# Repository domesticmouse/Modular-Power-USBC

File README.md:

# Modular-Power-USBC

## Project Overview
This project provides a compact, high-efficiency power solution for modular electronics (such as Eurorack synthesizers or analog prototyping boards). It converts standard **5V USB-C power** into clean, dual **±12V rails**.

### Key Features
- **USB-C Input:** Uses a power-only 6-pin receptacle for durability and simplicity.
- **Dual Rail Output:** Provides ±12V at up to 83mA per rail (2W total).
- **Comprehensive Protection:** Features overcurrent, reverse polarity, and back-drive protection.
- **Controlled Startup:** Integrated load switch with a physical toggle for safe power-up.
- **Indicator LEDs:** Visual confirmation for both positive and negative rails.

### Main Technologies
- **EDA Tool:** KiCad (Project files version 20260306, KiCad 10.0 or newer).
- **Major Components:**
  - **DC-DC Converter:** `A0512S-2WR2` (Isolated 2W module).
  - **Ideal Diode:** `LM66100` (Reverse polarity & back-drive protection).
  - **Load Switch:** `TPS22918` (Gated power control).
  - **Filtering:** Ferrite bead and 0805 SMD decoupling capacitors.
  - **Protection:** Resettable Polyfuse (`F1`).

## Circuit Architecture
The power path is designed for reliability and safety:

1.  **Input & Filtering:** 5V enters via `J1`. It is immediately protected by a Polyfuse and filtered by a Ferrite Bead to reduce high-frequency noise.
2.  **Polarity Protection:** An `LM66100` ideal diode provides extremely low-loss protection against reverse voltage on the input.
3.  **Gated Control:** The `TPS22918` load switch acts as the master gate. A physical SPDT slide switch (`SW1`) controls the enable pin, allowing the user to safely toggle the ±12V rails.
4.  **Isolated Conversion:** The `A0512S-2WR2` performs the heavy lifting, converting the 5V input to isolated ±12V outputs. This isolation helps prevent ground loops between the USB source and the analog circuitry.
5.  **Output Rail:** The dual rails are broken out to 2.54mm headers (`J2`, `J3`) for plugging into a breadboard.

## Directory Structure
- `Modular-Power-USBC.kicad_sch`: Main schematic file.
- `Modular-Power-USBC.kicad_pcb`: PCB layout file.
- `Modular-Power-USBC.pretty/`: Local footprint library for custom components.
- `ModularPower.kicad_sym`: Local symbol library.
- `production/`: Fabrication-ready files (Gerbers, BOM, Pick-and-Place).

## Project Status
- **Schematic:** Functional design complete.
- **ERC Status:** 1 Error (Pin 2 of PS1 not driven). Note: This is an ERC artifact due to a missing `PWR_FLAG` on the `GND` net; the electrical connection is correct.
- **Layout:** Complete.

## Building and Production
### KiCad Workflow
1. Open `Modular-Power-USBC.kicad_pro` in KiCad 10.0+.
2. Fabrication files are generated using the **KiCad Fabrication Toolkit** in the `production/` folder.
3. An **Interactive HTML BOM** is available in `bom/ibom.html` for hand-assembly.

## Development Conventions
- **Components:** Prefer LCSC part numbers (documented in `bom.csv` and component properties) for optimized sourcing via JLCPCB.
- **Footprints:** Custom footprints are maintained in the local `.pretty` library.

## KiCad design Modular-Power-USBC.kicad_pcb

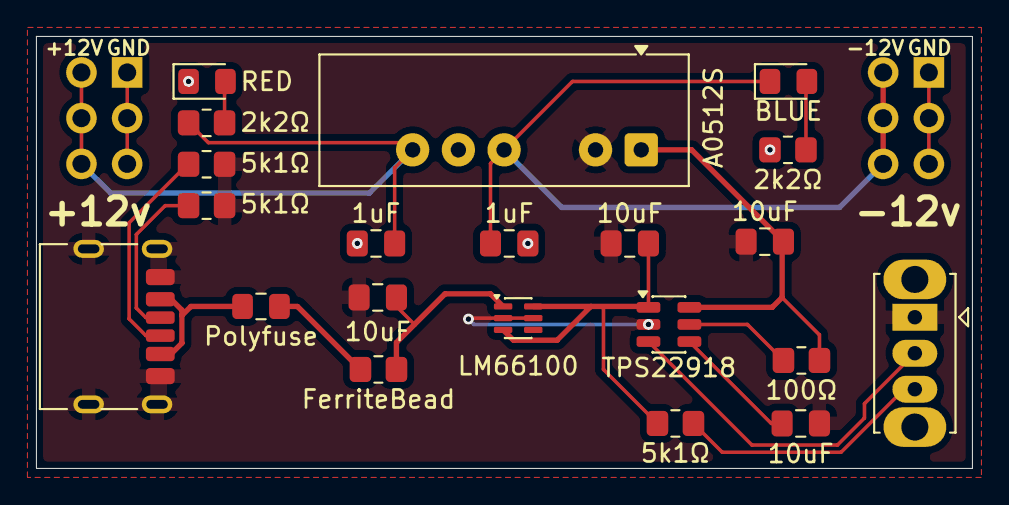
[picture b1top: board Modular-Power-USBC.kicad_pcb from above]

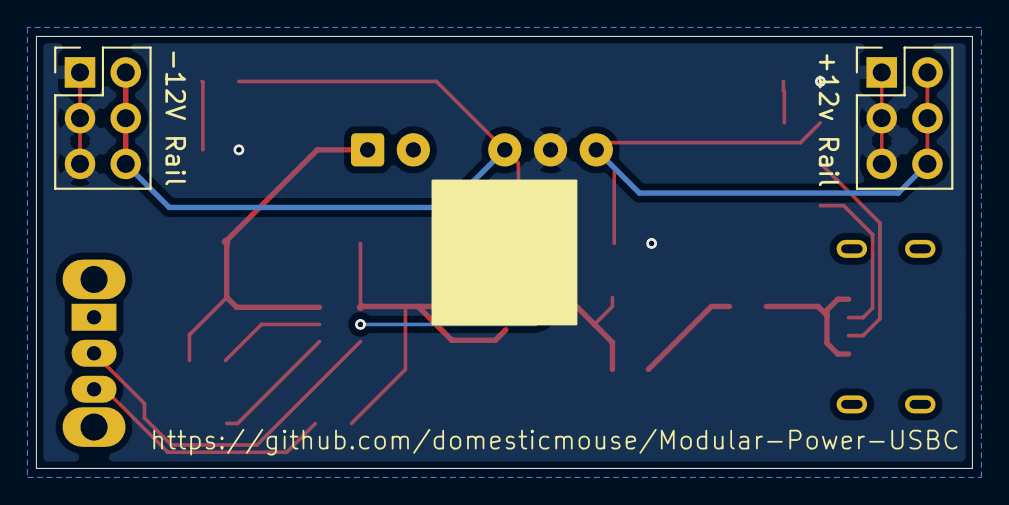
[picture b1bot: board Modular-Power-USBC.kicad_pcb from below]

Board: 2 copper layers, 52.0 x 24.0 mm, 23 parts (2 on the bottom side), 17 nets.

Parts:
C1, C2, C3, C6: 10uF; C_0805_2012Metric_Pad1.18x1.45mm_HandSolder
C4, C5: 1uF; C_0805_2012Metric_Pad1.18x1.45mm_HandSolder
D1: RED; LED_0805_2012Metric_Pad1.15x1.40mm_HandSolder
D2: BLUE; LED_0805_2012Metric_Pad1.15x1.40mm_HandSolder
F1: Polyfuse; Fuse_0805_2012Metric_Pad1.15x1.40mm_HandSolder
FB1: FerriteBead; FerriteBead_0805_2012Metric_Pad1.20x1.40mm_HandSolder
J1: USB_C_Receptacle_PowerOnly_6P; USB_C_Receptacle_HRO_TYPE-C-31-M-17
J2: +12v Rail; PinHeader_2x03_P2.54mm_Vertical
J3: -12V Rail; PinHeader_2x03_P2.54mm_Vertical
PS1: A0512S; Converter_DCDC_XP_POWER-IAxxxxS_THT
R1, R2, R5: 5k1Ω; R_0805_2012Metric_Pad1.20x1.40mm_HandSolder
R3, R4: 2k2Ω; R_0805_2012Metric_Pad1.20x1.40mm_HandSolder
R6: 100Ω; R_0805_2012Metric_Pad1.20x1.40mm_HandSolder
SW1: SW_SPDT; SW_Slide_SPDT_Straight_CK_OS102011MS2Q
U1: LM66100; SOT-363_SC-70-6
U2: TPS22918; SOT-23-6

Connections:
+5V: C3.1, PS1.1 (+Vin), R6.2, U2.6 (VOUT)
+12V: C4.1, J2.2, J2.4, J2.6, PS1.6 (+Vout), R3.1
-12V: C5.2, D2.1 (K), J3.2, J3.4, J3.6, PS1.4 (-Vout)
/CC1: J1.A5 (CC1), R2.1
/CC2: J1.B5 (CC2), R1.1
/VBUS: F1.1, J1.A9 (VBUS), J1.B9 (VBUS)
/VBUS_Protected: C2.1, R5.1, U1.3 (~CE), U1.6 (VOUT), U2.1 (VIN)
GND: C1.2, C2.2, C3.2, C6.2, J1.A12 (GND), J1.B12 (GND), J1.SH (SHIELD), PS1.2 (-Vin), R1.2, R2.2, SW1.1 (A), U1.2 (GND), U1.5 (ST), U2.2 (GND)
GNDA: C4.2, C5.1, D1.1 (K), J2.1, J2.3, J2.5, J3.1, J3.3, J3.5, PS1.5 (0V), R4.1
unnamed: D1.2 (A), R3.2
unnamed: D2.2 (A), R4.2
unnamed: F1.2, FB1.1
unnamed: SW1.2 (B), U2.3 (ON)
unnamed: R5.2, SW1.3 (C)
unnamed: C1.1, FB1.2, U1.1 (VIN)
unnamed: C6.1, U2.4 (CT)
unnamed: R6.1, U2.5 (QOD)

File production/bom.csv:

Designator,Footprint,Quantity,Value,LCSC Part #
"C1, C2, C3, C6",0805,4,10uF,C6119887
"C4, C5",0805,2,1uF,C116352
D1,0805,1,RED,C84256
D2,0805,1,BLUE,C84259
F1,0805,1,Polyfuse,C22363531
FB1,FerriteBead_0805_2012Metric_Pad1.20x1.40mm_HandSolder,1,FerriteBead,C76818
J1,USB_C_Receptacle_HRO_TYPE-C-31-M-17,1,USB_C_Receptacle_PowerOnly_6P,C668623
J2,PinHeader_2x03_P2.54mm_Vertical,1,+12v Rail,C7501274
J3,PinHeader_2x03_P2.54mm_Vertical,1,-12V Rail,C7501274
PS1,Converter_DCDC_XP_POWER-IAxxxxS_THT,1,A0512S,C19272708
"R1, R2, R5",0805,3,5k1Ω,C27834
"R3, R4",0805,2,2k2Ω,C2907303
R6,0805,1,100Ω,C2907294
SW1,SW_Slide_SPDT_Straight_CK_OS102011MS2Q,1,SW_SPDT,C2939725
U1,SOT-363_SC-70-6,1,LM66100,C2869734
U2,SOT-23-6,1,TPS22918,C131941

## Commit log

2026-04-30 Add switch
2026-04-30 Generate production files
2026-04-30 Create LICENSE
2026-04-30 Add README and fixup traces and symbols
2026-04-30 Drop redundant cap
2026-05-01 Clean up circuit with Gemini's assistance
2026-05-01 Add LCSC part numbers
2026-05-01 Update for production
